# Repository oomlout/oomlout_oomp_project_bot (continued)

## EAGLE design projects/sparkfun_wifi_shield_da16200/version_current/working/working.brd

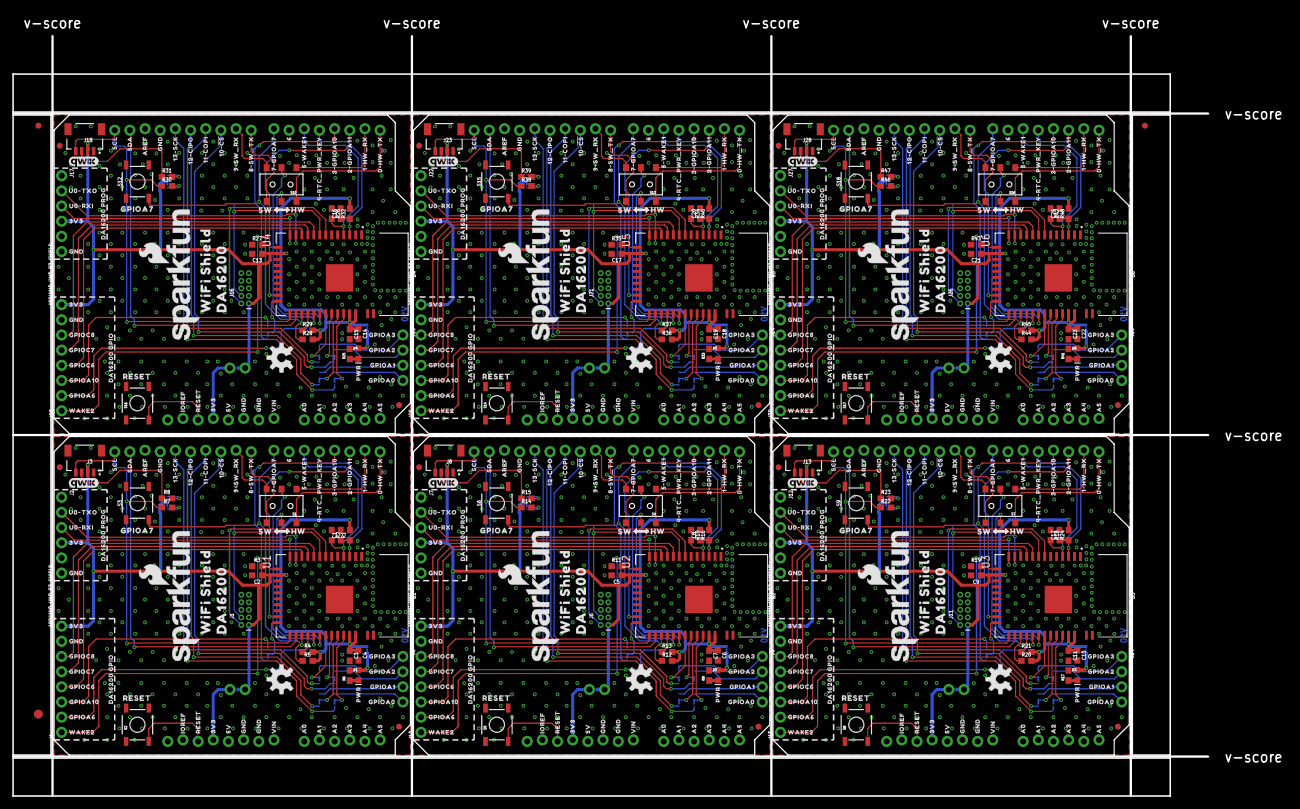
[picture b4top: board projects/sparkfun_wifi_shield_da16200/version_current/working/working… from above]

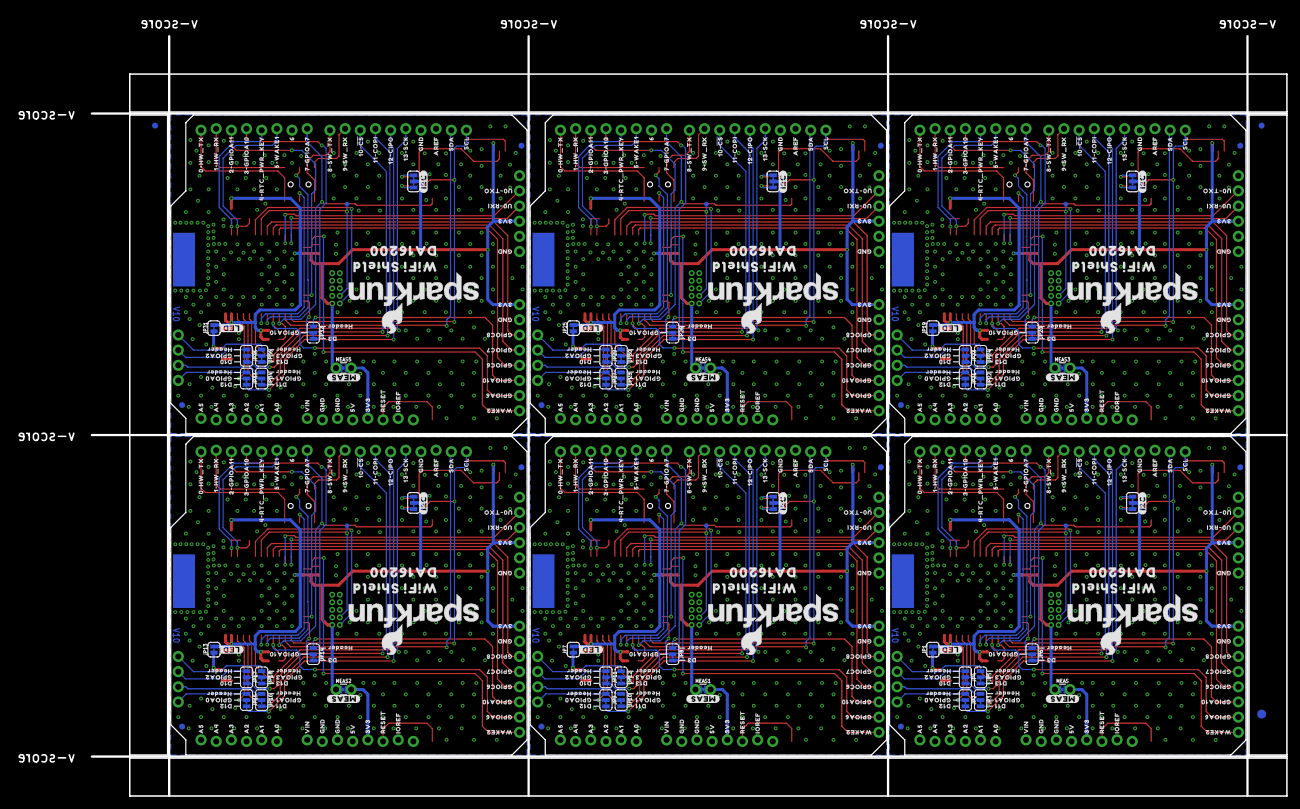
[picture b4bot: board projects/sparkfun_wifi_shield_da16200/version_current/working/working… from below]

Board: 2 copper layers, 200.2 x 127.3 mm, 960 parts (453 on the bottom side), 264 nets.

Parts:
B1, B2, B3, B4, B5, B6: ARDUINO_UNO_R3_SHIELD; UNO_R3_SHIELD_NOLABELS_LOCK
C1, C8, C12, C16, C20, C24: DNP; 0603
C2, C3, C5, C7, C9, C11, C13, C15, C17, C19, C21, C23: 1uF; 0603
C4, C6, C10, C14, C18, C22: 10uF; 0603
D1, D2, D3, D4, D5, D6: RED; LED-0603
E$1, E$2, E$3, E$4: FIDUCIAL-1X2
E$5, E$6: FIDUCIAL-1.5X3
FD1, FD2, FD3, FD4, FD5, FD6, FD7, FD8, FD9, FD10, FD11, FD12, FD13, FD14, FD15, FD16, FD17, FD18, FD19, FD20, FD21, FD22, FD23, FD24: FIDUCIAL1X2; FIDUCIAL-1X2
I2C, I2C1, I2C2, I2C3, I2C4, I2C5: SMT-JUMPER_3_2-NC_TRACE_SILK
J1, J6, J11, J16, J21, J26: CORTEX_JTAG_DEBUG; 2X5-PTH-1.27MM-NO_SILK
J2, J7, J12, J17, J22, J27: 1X06_NO_SILK
J3, J8, J13, J18, J23, J28: QWIIC_RA; JST04_1MM_RA
J4, J10, J15, J20, J25, J30: 1X08_NO_SILK
J5, J9, J14, J19, J24, J29: 1X04_NO_SILK
JP1, JP7, JP13, JP19, JP25, JP31: SMT-JUMPER_2_NC_TRACE_SILK
JP2, JP3, JP4, JP5, JP6, JP8, JP9, JP10, JP11, JP12, JP14, JP15, JP16, JP17, JP18, JP20, JP21, JP22, JP23, JP24, JP26, JP27, JP28, JP29, JP30, JP32, JP33, JP34, JP35, JP36: SMT-JUMPER_3_1-NC_TRACE_SILK
LOGO1, LOGO3, LOGO5, LOGO7, LOGO9, LOGO11, LOGO13, LOGO15, LOGO17, LOGO19, LOGO21, LOGO23: SFE_LOGO_NAME_FLAME.2_INCH; SFE_LOGO_NAME_FLAME_.2
LOGO2, LOGO6, LOGO10, LOGO14, LOGO18, LOGO22: OSHW-LOGOM; OSHW-LOGO-M
LOGO4, LOGO8, LOGO12, LOGO16, LOGO20, LOGO24: QWIIC_LOGO_5MM; QWIIC_5MM
MEAS, MEAS1, MEAS2, MEAS3, MEAS4, MEAS5: COMBO-JUMPER_2_NC_TRACE
R1, R16, R24, R32, R40, R48: DNP; 0603
R2, R3, R4, R5, R7, R8, R10, R11, R12, R13, R14, R15, R18, R19, R20, R21, R22, R23, R26, R27, R28, R29, R30, R31, R34, R35, R36, R37, R38, R39, R42, R43, R44, R45, R46, R47: 4.7k; 0603
R6, R9, R17, R25, R33, R41: 200; 0603
S1, S4, S7, S10, S13, S16: DPDT; SWITCH_DPDT_SMD_AYZ0202
S2, S5, S8, S11, S14, S17: Reset; TACTILE_SWITCH_SMD_5.2MM
S3, S6, S9, S12, S15, S18: TACTILE_SWITCH_SMD_5.2MM
TP1, TP2, TP3, TP4, TP5, TP6: PAD.03X.03
U1, U2, U3, U4, U5, U6: DA16200MOD; XCVR_DA16200MOD-AAC4WA32
U$1, U$16, U$22, U$162, U$239, U$281, U$358, U$400, U$477, U$519, U$596, U$638: IOREF0
U$2, U$19, U$67, U$163, U$240, U$282, U$359, U$401, U$478, U$520, U$597, U$639: RESET0
U$3, U$37, U$39, U$41, U$85, U$87, U$110, U$152, U$155, U$164, U$191, U$193, U$241, U$271, U$274, U$283, U$310, U$312, U$360, U$390, U$393, U$402, U$429, U$431, U$479, U$509, U$512, U$521, U$548, U$550, U$598, U$628, U$631, U$640, U$667, U$669: 3V30
U$4, U$55, U$111, U$165, U$242, U$284, U$361, U$403, U$480, U$522, U$599, U$641: 5V0
U$5, U$6, U$28, U$40, U$52, U$56, U$57, U$79, U$86, U$88, U$112, U$113, U$140, U$153, U$154, U$166, U$167, U$185, U$192, U$194, U$243, U$244, U$259, U$272, U$273, U$285, U$286, U$304, U$311, U$313, U$362, U$363, U$378, U$391, U$392, U$404, U$405, U$423, U$430, U$432, U$481, U$482, U$497, U$510, U$511, U$523, U$524, U$542, U$549, U$551, U$600, U$601, U$616, U$629, U$630, U$642, U$643, U$661, U$668, U$670: GND0
U$7, U$58, U$126, U$168, U$245, U$287, U$364, U$406, U$483, U$525, U$602, U$644: VIN0
U$8, U$59, U$127, U$169, U$246, U$288, U$365, U$407, U$484, U$526, U$603, U$645: A00
U$9, U$60, U$128, U$170, U$247, U$289, U$366, U$408, U$485, U$527, U$604, U$646: A10
U$10, U$61, U$129, U$171, U$248, U$290, U$367, U$409, U$486, U$528, U$605, U$647: A20
U$11, U$62, U$130, U$172, U$249, U$291, U$368, U$410, U$487, U$529, U$606, U$648: A30
U$12, U$63, U$131, U$173, U$250, U$292, U$369, U$411, U$488, U$530, U$607, U$649: A40
U$13, U$64, U$132, U$174, U$251, U$293, U$370, U$412, U$489, U$531, U$608, U$650: A50
U$14, U$65, U$133, U$175, U$252, U$294, U$371, U$413, U$490, U$532, U$609, U$651: 0#HW_TX0
U$15, U$66, U$134, U$176, U$253, U$295, U$372, U$414, U$491, U$533, U$610, U$652: 1#HW_RX0
U$17, U$95, U$158, U$199, U$277, U$318, U$396, U$437, U$515, U$556, U$634, U$675: GPIOA60
U$18, U$70, U$231, U$234, U$350, U$353, U$469, U$472, U$588, U$591, U$707, U$710: 4#RTC_PWR_KEY0
U$20, U$73, U$159, U$179, U$278, U$298, U$397, U$417, U$516, U$536, U$635, U$655: 8#SW_TX0
U$21, U$72, U$135, U$178, U$254, U$297, U$373, U$416, U$492, U$535, U$611, U$654: 7#GPIOA70
U$23, U$33, U$232, U$233, U$351, U$352, U$470, U$471, U$589, U$590, U$708, U$709: 5#WAKE10
U$24, U$75, U$136, U$181, U$255, U$300, U$374, U$419, U$493, U$538, U$612, U$657: 10##CS#0
U$25, U$76, U$137, U$182, U$256, U$301, U$375, U$420, U$494, U$539, U$613, U$658: 11#COPI0
U$26, U$77, U$138, U$183, U$257, U$302, U$376, U$421, U$495, U$540, U$614, U$659: 12#CIPO0
U$27, U$78, U$139, U$184, U$258, U$303, U$377, U$422, U$496, U$541, U$615, U$660: 13#SCK0
U$29, U$80, U$141, U$186, U$260, U$305, U$379, U$424, U$498, U$543, U$617, U$662: AREF0
U$30, U$81, U$142, U$187, U$261, U$306, U$380, U$425, U$499, U$544, U$618, U$663: SDA0
U$31, U$82, U$143, U$188, U$262, U$307, U$381, U$426, U$500, U$545, U$619, U$664: SCL0
U$32, U$74, U$160, U$180, U$279, U$299, U$398, U$418, U$517, U$537, U$636, U$656: 9#SW_RX0
U$34, U$144, U$263, U$382, U$501, U$620: GPIOA70
U$35, U$48, U$235, U$236, U$354, U$355, U$473, U$474, U$592, U$593, U$711, U$712: WAKE20
U$36, U$151, U$270, U$389, U$508, U$627: RESET_0
U$38, U$71, U$161, U$177, U$280, U$296, U$399, U$415, U$518, U$534, U$637, U$653: 60
U$42, U$156, U$275, U$394, U$513, U$632: HW0
U$43, U$157, U$276, U$395, U$514, U$633: SW0
U$44, U$89, U$145, U$195, U$264, U$314, U$383, U$433, U$502, U$552, U$621, U$671: GPIOC80
U$45, U$90, U$146, U$196, U$265, U$315, U$384, U$434, U$503, U$553, U$622, U$672: GPIOC70
U$46, U$91, U$147, U$197, U$266, U$316, U$385, U$435, U$504, U$554, U$623, U$673: GPIOC60
U$47, U$69, U$92, U$148, U$198, U$207, U$267, U$317, U$326, U$386, U$436, U$445, U$505, U$555, U$564, U$624, U$674, U$683: GPIOA100
U$49, U$214, U$333, U$452, U$571, U$690: #I2C#0
U$50, U$109, U$237, U$238, U$356, U$357, U$475, U$476, U$594, U$595, U$713, U$714: 2#GPIOA110
U$51, U$68, U$205, U$206, U$324, U$325, U$443, U$444, U$562, U$563, U$681, U$682: 3#GPIOA100
U$53, U$83, U$149, U$189, U$268, U$308, U$387, U$427, U$506, U$546, U$625, U$665: U0#TXO0
U$54, U$84, U$150, U$190, U$269, U$309, U$388, U$428, U$507, U$547, U$626, U$666: U0#RXI0
U$93, U$115, U$216, U$227, U$335, U$346, U$454, U$465, U$573, U$584, U$692, U$703: GPIOA00
U$94, U$114, U$215, U$228, U$334, U$347, U$453, U$466, U$572, U$585, U$691, U$704: GPIOA10
U$96, U$208, U$327, U$446, U$565, U$684: D30
U$97, U$200, U$319, U$438, U$557, U$676: #LED#0
U$98, U$201, U$320, U$439, U$558, U$677: #MEAS#0
U$99, U$202, U$321, U$440, U$559, U$678: PWR0
U$100, U$107, U$210, U$212, U$329, U$331, U$448, U$450, U$567, U$569, U$686, U$688: WIFI_SHIELD0
U$101, U$108, U$211, U$213, U$330, U$332, U$449, U$451, U$568, U$570, U$687, U$689: DA162000
U$102, U$116, U$217, U$229, U$336, U$348, U$455, U$467, U$574, U$586, U$693, U$705: GPIOA20
U$103, U$117, U$218, U$230, U$337, U$349, U$456, U$468, U$575, U$587, U$694, U$706: GPIOA30
U$104, U$203, U$322, U$441, U$560, U$679: DA16200_GPIO0
U$105, U$204, U$323, U$442, U$561, U$680: DA16200_PROG0
U$106, U$118, U$119, U$120, U$121, U$209, U$219, U$220, U$221, U$222, U$328, U$338, U$339, U$340, U$341, U$447, U$457, U$458, U$459, U$460, U$566, U$576, U$577, U$578, U$579, U$685, U$695, U$696, U$697, U$698: HEADER0
U$122, U$223, U$342, U$461, U$580, U$699: D100
U$123, U$224, U$343, U$462, U$581, U$700: D110
U$124, U$225, U$344, U$463, U$582, U$701: D120
U$125, U$226, U$345, U$464, U$583, U$702: D130

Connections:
3.3V: C2.1, C3.1, C4.1, I2C.2, J1.1, J2.4, J3.2, J4.8, JP1.2, MEAS.1, MEAS.3, R1.2, R4.2, R5.2, U1.15, U1.34, U1.35
3.3V1: C5.1, C6.1, C7.1, I2C1.2, J6.1, J7.4, J8.2, J10.8, JP7.2, MEAS1.1, MEAS1.3, R12.2, R13.2, R16.2, U2.15, U2.34, U2.35
3.3V2: C9.1, C10.1, C11.1, I2C2.2, J11.1, J12.4, J13.2, J15.8, JP13.2, MEAS2.1, MEAS2.3, R20.2, R21.2, R24.2, U3.15, U3.34, U3.35
3.3V3: C13.1, C14.1, C15.1, I2C3.2, J16.1, J17.4, J18.2, J20.8, JP19.2, MEAS3.1, MEAS3.3, R28.2, R29.2, R32.2, U4.15, U4.34, U4.35
3.3V4: C17.1, C18.1, C19.1, I2C4.2, J21.1, J22.4, J23.2, J25.8, JP25.2, MEAS4.1, MEAS4.3, R36.2, R37.2, R40.2, U5.15, U5.34, U5.35
3.3V5: C21.1, C22.1, C23.1, I2C5.2, J26.1, J27.4, J28.2, J30.8, JP31.2, MEAS5.1, MEAS5.3, R44.2, R45.2, R48.2, U6.15, U6.34, U6.35
ARD_GPIOA1: B2.D3, JP8.3
ARD_GPIOA2: B3.D3, JP14.3
ARD_GPIOA3: B4.D3, JP20.3
ARD_GPIOA4: B5.D3, JP26.3
ARD_GPIOA5: B6.D3, JP32.3
ARD_GPIOA10: B1.D3, JP6.3
ARD_HW_RX: B1.RX, S1.1
ARD_HW_RX1: B2.RX, S4.1
ARD_HW_RX2: B3.RX, S7.1
ARD_HW_RX3: B4.RX, S10.1
ARD_HW_RX4: B5.RX, S13.1
ARD_HW_RX5: B6.RX, S16.1
ARD_HW_TX: B1.TX, S1.4
ARD_HW_TX1: B2.TX, S4.4
ARD_HW_TX2: B3.TX, S7.4
ARD_HW_TX3: B4.TX, S10.4
ARD_HW_TX4: B5.TX, S13.4
ARD_HW_TX5: B6.TX, S16.4
ARD_RESET: B1.RES, S2.3
ARD_RESET1: B2.RES, S5.3
ARD_RESET2: B3.RES, S8.3
ARD_RESET3: B4.RES, S11.3
ARD_RESET4: B5.RES, S14.3
ARD_RESET5: B6.RES, S17.3
ARD_SCL: B1.SCL, J3.4, R7.1, U1.24
ARD_SCL1: B2.SCL, J8.4, R14.1, U2.24
ARD_SCL2: B3.SCL, J13.4, R22.1, U3.24
ARD_SCL3: B4.SCL, J18.4, R30.1, U4.24
ARD_SCL4: B5.SCL, J23.4, R38.1, U5.24
ARD_SCL5: B6.SCL, J28.4, R46.1, U6.24
ARD_SDA: B1.SDA, J3.3, R8.1, U1.25
ARD_SDA1: B2.SDA, J8.3, R15.1, U2.25
ARD_SDA2: B3.SDA, J13.3, R23.1, U3.25
ARD_SDA3: B4.SDA, J18.3, R31.1, U4.25
ARD_SDA4: B5.SDA, J23.3, R39.1, U5.25
ARD_SDA5: B6.SDA, J28.3, R47.1, U6.25
ARD_SW_RX: B1.D8, S1.3
ARD_SW_RX1: B2.D8, S4.3
ARD_SW_RX2: B3.D8, S7.3
ARD_SW_RX3: B4.D8, S10.3
ARD_SW_RX4: B5.D8, S13.3
ARD_SW_RX5: B6.D8, S16.3
ARD_SW_TX: B1.D9, S1.6
ARD_SW_TX1: B2.D9, S4.6
ARD_SW_TX2: B3.D9, S7.6
ARD_SW_TX3: B4.D9, S10.6
ARD_SW_TX4: B5.D9, S13.6
ARD_SW_TX5: B6.D9, S16.6
GND: B1.GND@0, B1.GND@1, B1.GND@2, C1.2, C2.2, C3.2, C4.2, J1.3, J1.5, J1.9, J2.6, J3.1, J4.7, R2.1, R3.1, R6.2, S2.1, S3.1, U1.2, U1.ANT_GND, U1.GND
GND1: B2.GND@0, B2.GND@1, B2.GND@2, C5.2, C6.2, C7.2, C8.2, J6.3, J6.5, J6.9, J7.6, J8.1, J10.7, R9.2, R10.1, R11.1, S5.1, S6.1, U2.2, U2.ANT_GND, U2.GND
GND2: B3.GND@0, B3.GND@1, B3.GND@2, C9.2, C10.2, C11.2, C12.2, J11.3, J11.5, J11.9, J12.6, J13.1, J15.7, R17.2, R18.1, R19.1, S8.1, S9.1, U3.2, U3.ANT_GND, U3.GND
GND3: B4.GND@0, B4.GND@1, B4.GND@2, C13.2, C14.2, C15.2, C16.2, J16.3, J16.5, J16.9, J17.6, J18.1, J20.7, R25.2, R26.1, R27.1, S11.1, S12.1, U4.2, U4.ANT_GND, U4.GND
GND4: B5.GND@0, B5.GND@1, B5.GND@2, C17.2, C18.2, C19.2, C20.2, J21.3, J21.5, J21.9, J22.6, J23.1, J25.7, R33.2, R34.1, R35.1, S14.1, S15.1, U5.2, U5.ANT_GND, U5.GND
GND5: B6.GND@0, B6.GND@1, B6.GND@2, C21.2, C22.2, C23.2, C24.2, J26.3, J26.5, J26.9, J27.6, J28.1, J30.7, R41.2, R42.1, R43.1, S17.1, S18.1, U6.2, U6.ANT_GND, U6.GND
GPIOA0: JP2.2, U1.33
GPIOA1: JP3.2, U1.32
GPIOA2: JP4.2, U1.31
GPIOA3: JP5.2, U1.30
GPIOA4: B2.D7, R12.1, S6.3, U2.26
GPIOA5: JP8.2, U2.23
GPIOA6: B2.D2, U2.22
GPIOA7: B1.D7, R5.1, S3.3, U1.26
GPIOA8: JP9.2, U2.33
GPIOA9: JP10.2, U2.32
GPIOA10: JP6.2, U1.23
GPIOA11: B1.D2, U1.22
GPIOA12: JP11.2, U2.31
GPIOA13: JP12.2, U2.30
GPIOA14: B3.D7, R20.1, S9.3, U3.26
GPIOA15: JP14.2, U3.23
GPIOA16: B3.D2, U3.22
GPIOA17: JP15.2, U3.33
GPIOA18: JP16.2, U3.32
GPIOA19: JP17.2, U3.31
GPIOA20: JP18.2, U3.30
GPIOA21: B4.D7, R28.1, S12.3, U4.26
GPIOA22: JP20.2, U4.23
GPIOA23: B4.D2, U4.22
GPIOA24: JP21.2, U4.33
GPIOA25: JP22.2, U4.32
GPIOA26: JP23.2, U4.31
GPIOA27: JP24.2, U4.30
GPIOA28: B5.D7, R36.1, S15.3, U5.26
GPIOA29: JP26.2, U5.23
GPIOA30: B5.D2, U5.22
GPIOA31: JP27.2, U5.33
GPIOA32: JP28.2, U5.32
GPIOA33: JP29.2, U5.31
GPIOA34: JP30.2, U5.30
GPIOA35: B6.D7, R44.1, S18.3, U6.26
GPIOA36: JP32.2, U6.23
GPIOA37: B6.D2, U6.22
GPIOA38: JP33.2, U6.33
GPIOA39: JP34.2, U6.32
GPIOA40: JP35.2, U6.31
GPIOA41: JP36.2, U6.30
HDR_GPIOA0: J5.4, JP2.1
HDR_GPIOA1: J5.3, JP3.1
HDR_GPIOA2: J5.2, JP4.1
HDR_GPIOA3: J5.1, JP5.1
HDR_GPIOA4: J9.4, JP9.1
HDR_GPIOA5: J9.3, JP10.1
HDR_GPIOA6: J4.2, R4.1, U1.27
HDR_GPIOA7: J10.3, JP8.1
HDR_GPIOA8: J10.2, R13.1, U2.27
HDR_GPIOA9: J9.2, JP11.1
HDR_GPIOA10: J4.3, JP6.1
HDR_GPIOA11: J9.1, JP12.1
HDR_GPIOA12: J14.4, JP15.1
HDR_GPIOA13: J14.3, JP16.1
HDR_GPIOA14: J15.3, JP14.1
HDR_GPIOA15: J15.2, R21.1, U3.27
HDR_GPIOA16: J14.2, JP17.1
HDR_GPIOA17: J14.1, JP18.1
HDR_GPIOA18: J19.4, JP21.1
HDR_GPIOA19: J19.3, JP22.1
HDR_GPIOA20: J20.3, JP20.1
HDR_GPIOA21: J20.2, R29.1, U4.27
HDR_GPIOA22: J19.2, JP23.1
HDR_GPIOA23: J19.1, JP24.1
HDR_GPIOA24: J24.4, JP27.1
HDR_GPIOA25: J24.3, JP28.1
HDR_GPIOA26: J25.3, JP26.1
HDR_GPIOA27: J25.2, R37.1, U5.27
HDR_GPIOA28: J24.2, JP29.1
HDR_GPIOA29: J24.1, JP30.1
HDR_GPIOA30: J29.4, JP33.1
HDR_GPIOA31: J29.3, JP34.1
HDR_GPIOA32: J30.3, JP32.1
HDR_GPIOA33: J30.2, R45.1, U6.27
HDR_GPIOA34: J29.2, JP35.1
HDR_GPIOA35: J29.1, JP36.1
HDR_GPIOC1: J10.4, U2.11
HDR_GPIOC2: J10.5, U2.10
HDR_GPIOC3: J10.6, U2.9
HDR_GPIOC4: J15.4, U3.11
HDR_GPIOC5: J15.5, U3.10
HDR_GPIOC6: J4.4, U1.11
HDR_GPIOC7: J4.5, U1.10
HDR_GPIOC8: J4.6, U1.9
HDR_GPIOC9: J15.6, U3.9
HDR_GPIOC10: J20.4, U4.11
HDR_GPIOC11: J20.5, U4.10
HDR_GPIOC12: J20.6, U4.9
HDR_GPIOC13: J25.4, U5.11
HDR_GPIOC14: J25.5, U5.10
HDR_GPIOC15: J25.6, U5.9
HDR_GPIOC16: J30.4, U6.11
HDR_GPIOC17: J30.5, U6.10
HDR_GPIOC18: J30.6, U6.9
HDR_RTC_WAKE1: J10.1, R11.2, U2.14
HDR_RTC_WAKE2: J4.1, R3.2, U1.14
HDR_RTC_WAKE3: J15.1, R19.2, U3.14
HDR_RTC_WAKE4: J20.1, R27.2, U4.14
HDR_RTC_WAKE5: J25.1, R35.2, U5.14
HDR_RTC_WAKE6: J30.1, R43.2, U6.14
unnamed: B1.3.3V, MEAS.2, MEAS.4
unnamed: D1.A, JP1.1
unnamed: I2C.3, R7.2
unnamed: I2C.1, R8.2
unnamed: D1.C, R6.1
unnamed: D2.C, R9.1
unnamed: B2.3.3V, MEAS1.2, MEAS1.4
unnamed: D2.A, JP7.1
unnamed: I2C1.3, R14.2
unnamed: I2C1.1, R15.2
unnamed: D3.C, R17.1
unnamed: B3.3.3V, MEAS2.2, MEAS2.4
unnamed: D3.A, JP13.1
unnamed: I2C2.3, R22.2
unnamed: I2C2.1, R23.2
unnamed: D4.C, R25.1
unnamed: B4.3.3V, MEAS3.2, MEAS3.4
unnamed: D4.A, JP19.1
unnamed: I2C3.3, R30.2
unnamed: I2C3.1, R31.2
unnamed: D5.C, R33.1
unnamed: B5.3.3V, MEAS4.2, MEAS4.4
unnamed: D5.A, JP25.1
unnamed: I2C4.3, R38.2
unnamed: I2C4.1, R39.2
unnamed: D6.C, R41.1
unnamed: B6.3.3V, MEAS5.2, MEAS5.4
unnamed: D6.A, JP31.1
unnamed: I2C5.3, R46.2
unnamed: I2C5.1, R47.2
RTC_PWR_KEY: B1.D4, C1.1, R1.1, U1.3
RTC_PWR_KEY1: B2.D4, C8.1, R16.1, U2.3
RTC_PWR_KEY2: B3.D4, C12.1, R24.1, U3.3
RTC_PWR_KEY3: B4.D4, C16.1, R32.1, U4.3
RTC_PWR_KEY4: B5.D4, C20.1, R40.1, U5.3
RTC_PWR_KEY5: B6.D4, C24.1, R48.1, U6.3
RTC_WAKE1: B1.D5, R2.2, U1.4
RTC_WAKE2: B2.D5, R10.2, U2.4
RTC_WAKE3: B3.D5, R18.2, U3.4
RTC_WAKE4: B4.D5, R26.2, U4.4
RTC_WAKE5: B5.D5, R34.2, U5.4
RTC_WAKE6: B6.D5, R42.2, U6.4
SPI_CIPO: B1.D12, JP2.3
SPI_CIPO1: B2.D12, JP9.3
SPI_CIPO2: B3.D12, JP15.3
SPI_CIPO3: B4.D12, JP21.3
SPI_CIPO4: B5.D12, JP27.3
SPI_CIPO5: B6.D12, JP33.3
SPI_COPI: B1.D11, JP3.3
SPI_COPI1: B2.D11, JP10.3
SPI_COPI2: B3.D11, JP16.3
SPI_COPI3: B4.D11, JP22.3
SPI_COPI4: B5.D11, JP28.3
SPI_COPI5: B6.D11, JP34.3
SPI_CS: B1.D10, JP4.3
SPI_CS1: B2.D10, JP11.3
SPI_CS2: B3.D10, JP17.3
SPI_CS3: B4.D10, JP23.3
SPI_CS4: B5.D10, JP29.3
SPI_CS5: B6.D10, JP35.3
SPI_SCK: B1.D13, JP5.3
SPI_SCK1: B2.D13, JP12.3
SPI_SCK2: B3.D13, JP18.3
SPI_SCK3: B4.D13, JP24.3
SPI_SCK4: B5.D13, JP30.3
SPI_SCK5: B6.D13, JP36.3
TCLK: J1.4, TP1.1, U1.8
TCLK1: J6.4, TP2.1, U2.8
TCLK2: J11.4, TP3.1, U3.8
TCLK3: J16.4, TP4.1, U4.8
TCLK4: J21.4, TP5.1, U5.8
TCLK5: J26.4, TP6.1, U6.8
TMS: J1.2, U1.7
TMS1: J6.2, U2.7
TMS2: J11.2, U3.7
TMS3: J16.2, U4.7
TMS4: J21.2, U5.7
TMS5: J26.2, U6.7
U0RXI: J2.3, U1.13
U0RXI1: J7.3, U2.13
U0RXI2: J12.3, U3.13
U0RXI3: J17.3, U4.13
U0RXI4: J22.3, U5.13
U0RXI5: J27.3, U6.13
U0TXO: J2.2, U1.12
U0TXO1: J7.2, U2.12
U0TXO2: J12.2, U3.12
U0TXO3: J17.2, U4.12
U0TXO4: J22.2, U5.12
U0TXO5: J27.2, U6.12
U1RXI: S1.5, U1.28
U1RXI1: S4.5, U2.28
U1RXI2: S7.5, U3.28
U1RXI3: S10.5, U4.28
U1RXI4: S13.5, U5.28
U1RXI5: S16.5, U6.28
U1TXO: S1.2, U1.29
U1TXO1: S4.2, U2.29
U1TXO2: S7.2, U3.29
U1TXO3: S10.2, U4.29
U1TXO4: S13.2, U5.29
U1TXO5: S16.2, U6.29

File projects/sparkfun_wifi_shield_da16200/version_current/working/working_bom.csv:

"Id";"Designator";"Footprint";"Quantity";"Designation";"Supplier and ref";
1;"U$630,U$378,U$600,U$243,U$391,U$629,U$40,U$392,U$140,U$113,U$616,U$511,U$273,U$497,U$244,U$28,U$259,U$482,U$362,U$272,U$112,U$5,U$6,U$510,U$481,U$52,U$153,U$154,U$601,U$363,U$194,U$79,U$185,U$56,U$643,U$88,U$57,U$542,U$661,U$404,U$313,U$551,U$192,U$423,U$668,U$549,U$166,U$285,U$167,U$86,U$432,U$524,U$304,U$311,U$642,U$405,U$670,U$430,U$523,U$286";"GND0";60;"";;;
2;"S6,S15,S9,S3,S12,S18";"TACTILE_SWITCH_SMD_5.2MM";6;"";;;
3;"C13,C3,C21,C11,C17,C23,C7,C2,C5,C9,C15,C19";"0603";12;"1uF";;;
4;"J29,J5,J19,J14,J9,J24";"1X04_NO_SILK";6;"";;;
5;"C8,R48,R32,R24,C16,C20,C12,R16,R1,C1,R40,C24";"0603";12;"DNP";;;
6;"U$585,U$228,U$466,U$94,U$704,U$347,U$334,U$114,U$691,U$215,U$572,U$453";"GPIOA10";12;"";;;
7;"LOGO21,LOGO1,LOGO13,LOGO5,LOGO9,LOGO17,LOGO7,LOGO23,LOGO3,LOGO15,LOGO11,LOGO19";"SFE_LOGO_NAME_FLAME_.2";12;"SFE_LOGO_NAME_FLAME.2_INCH";;;
8;"E$3,E$1,E$4,E$2";"FIDUCIAL-1X2";4;"";;;
9;"U$589,U$232,U$23,U$470,U$351,U$708,U$352,U$233,U$471,U$709,U$33,U$590";"5#WAKE10";12;"";;;
10;"U$350,U$231,U$707,U$469,U$18,U$588,U$591,U$353,U$70,U$234,U$472,U$710";"4#RTC_PWR_KEY0";12;"";;;
11;"U$625,U$53,U$387,U$149,U$268,U$506,U$665,U$189,U$83,U$308,U$427,U$546";"U0#TXO0";12;"";;;
12;"U$133,U$14,U$490,U$252,U$371,U$609,U$175,U$294,U$532,U$651,U$413,U$65";"0#HW_TX0";12;"";;;
13;"U$10,U$605,U$486,U$129,U$248,U$367,U$409,U$290,U$528,U$647,U$61,U$171";"A20";12;"";;;
14;"U$142,U$380,U$499,U$30,U$618,U$261,U$663,U$187,U$425,U$306,U$544,U$81";"SDA0";12;"";;;
15;"LOGO4,LOGO16,LOGO12,LOGO24,LOGO8,LOGO20";"QWIIC_5MM";6;"QWIIC_LOGO_5MM";;;
16;"U$368,U$130,U$487,U$249,U$11,U$606,U$62,U$410,U$172,U$648,U$529,U$291";"A30";12;"";;;
17;"U$394,U$513,U$632,U$156,U$42,U$275";"HW0";6;"";;;
18;"J12,J17,J2,J22,J27,J7";"1X06_NO_SILK";6;"";;;
19;"C4,C22,C18,C10,C14,C6";"0603";6;"10uF";;;
20;"U$388,U$626,U$54,U$269,U$507,U$150,U$309,U$666,U$84,U$547,U$428,U$190";"U0#RXI0";12;"";;;
21;"U$203,U$322,U$441,U$679,U$104,U$560";"DA16200_GPIO0";6;"";;;
22;"U$610,U$491,U$253,U$372,U$15,U$134,U$414,U$533,U$295,U$652,U$66,U$176";"1#HW_RX0";12;"";;;
23;"U$680,U$105,U$204,U$561,U$442,U$323";"DA16200_PROG0";6;"";;;
24;"U$598,U$241,U$628,U$631,U$274,U$479,U$41,U$271,U$155,U$110,U$37,U$393,U$360,U$390,U$152,U$3,U$512,U$509,U$669,U$431,U$429,U$640,U$667,U$85,U$310,U$193,U$548,U$87,U$283,U$191,U$521,U$550,U$164,U$39,U$402,U$312";"3V30";36;"";;;
25;"J28,J13,J18,J23,J8,J3";"JST04_1MM_RA";6;"QWIIC_RA";;;
26;"R5,R7,R18,R15,R30,R31,R10,R8,R26,R37,R4,R19,R46,R2,R22,R29,R45,R39,R3,R11,R43,R21,R28,R44,R42,R20,R36,R47,R14,R13,R34,R27,R23,R35,R12,R38";"0603";36;"4.7k";;;
27;"J15,J4,J30,J25,J10,J20";"1X08_NO_SILK";6;"";;;
28;"U$383,U$502,U$44,U$621,U$264,U$145,U$552,U$671,U$195,U$89,U$314,U$433";"GPIOC80";12;"";;;
29;"B2,B1,B3,B4,B6,B5";"UNO_R3_SHIELD_NOLABELS_LOCK";6;"ARDUINO_UNO_R3_SHIELD";;;
30;"U$636,U$279,U$517,U$32,U$398,U$160,U$299,U$180,U$74,U$656,U$418,U$537";"9#SW_RX0";12;"";;;
31;"U$25,U$613,U$375,U$494,U$256,U$137,U$301,U$658,U$539,U$76,U$420,U$182";"11#COPI0";12;"";;;
32;"U$38,U$161,U$518,U$280,U$399,U$637,U$415,U$296,U$653,U$177,U$534,U$71";"60";12;"";;;
33;"U$348,U$229,U$102,U$705,U$586,U$467,U$693,U$217,U$574,U$336,U$116,U$455";"GPIOA20";12;"";;;
34;"FD11,FD7,FD15,FD3,FD23,FD9,FD19,FD5,FD17,FD21,FD13,FD1,FD12,FD4,FD6,FD18,FD16,FD14,FD8,FD10,FD22,FD2,FD20,FD24";"FIDUCIAL-1X2";24;"FIDUCIAL1X2";;;
35;"U6,U4,U5,U1,U3,U2";"XCVR_DA16200MOD-AAC4WA32";6;"DA16200MOD";;;
36;"D2,D3,D6,D1,D4,D5";"LED-0603";6;"RED";;;
37;"U$46,U$385,U$147,U$266,U$504,U$623,U$554,U$673,U$91,U$197,U$435,U$316";"GPIOC60";12;"";;;
38;"U$687,U$108,U$568,U$449,U$211,U$330,U$213,U$570,U$689,U$451,U$101,U$332";"DA162000";12;"";;;
39;"U$382,U$34,U$263,U$501,U$144,U$620";"GPIOA70";6;"";;;
40;"U$128,U$366,U$485,U$604,U$9,U$247,U$408,U$170,U$527,U$60,U$289,U$646";"A10";12;"";;;
41;"U$614,U$376,U$138,U$495,U$26,U$257,U$540,U$183,U$302,U$421,U$659,U$77";"12#CIPO0";12;"";;;
42;"U$602,U$126,U$364,U$483,U$245,U$7,U$287,U$406,U$644,U$58,U$168,U$525";"VIN0";12;"";;;
43;"U$597,U$2,U$478,U$359,U$67,U$240,U$282,U$401,U$520,U$163,U$639,U$19";"RESET0";12;"";;;
44;"U$617,U$260,U$29,U$498,U$141,U$379,U$662,U$424,U$80,U$543,U$186,U$305";"AREF0";12;"";;;
45;"R6,R41,R9,R25,R33,R17";"0603";6;"200";;;
46;"U$596,U$239,U$358,U$477,U$1,U$22,U$519,U$281,U$400,U$638,U$162,U$16";"IOREF0";12;"";;;
47;"LOGO14,LOGO6,LOGO22,LOGO10,LOGO2,LOGO18";"OSHW-LOGO-M";6;"OSHW-LOGOM";;;
48;"U$251,U$608,U$13,U$489,U$132,U$370,U$412,U$531,U$650,U$174,U$64,U$293";"A50";12;"";;;
49;"U$496,U$615,U$139,U$377,U$258,U$27,U$660,U$184,U$541,U$78,U$422,U$303";"13#SCK0";12;"";;;
50;"U$389,U$36,U$270,U$151,U$627,U$508";"RESET_0";6;"";;;
51;"U$635,U$278,U$20,U$516,U$159,U$397,U$73,U$536,U$417,U$298,U$655,U$179";"8#SW_TX0";12;"";;;
52;"U$714,U$109,U$238,U$476,U$595,U$357,U$237,U$50,U$594,U$475,U$713,U$356";"2#GPIOA110";12;"";;;
53;"J11,J6,J16,J26,J21,J1";"2X5-PTH-1.27MM-NO_SILK";6;"CORTEX_JTAG_DEBUG";;;
54;"U$45,U$622,U$265,U$384,U$146,U$503,U$434,U$553,U$196,U$672,U$315,U$90";"GPIOC70";12;"";;;
55;"U$277,U$17,U$396,U$634,U$158,U$515,U$318,U$95,U$675,U$437,U$556,U$199";"GPIOA60";12;"";;;
56;"U$276,U$395,U$157,U$514,U$633,U$43";"SW0";6;"";;;
57;"E$5,E$6";"FIDUCIAL-1.5X3";2;"";;;
58;"U$127,U$365,U$603,U$484,U$8,U$246,U$645,U$169,U$407,U$288,U$59,U$526";"A00";12;"";;;
59;"U$324,U$205,U$681,U$51,U$443,U$562,U$68,U$682,U$325,U$444,U$563,U$206";"3#GPIOA100";12;"";;;
60;"U$492,U$254,U$135,U$611,U$21,U$373,U$72,U$654,U$178,U$297,U$535,U$416";"7#GPIOA70";12;"";;;
61;"U$493,U$374,U$136,U$24,U$612,U$255,U$538,U$657,U$300,U$419,U$181,U$75";"10##CS#0";12;"";;;
62;"U$210,U$329,U$107,U$448,U$567,U$686,U$688,U$100,U$450,U$212,U$569,U$331";"WIFI_SHIELD0";12;"";;;
63;"U$619,U$143,U$31,U$500,U$381,U$262,U$545,U$188,U$664,U$307,U$426,U$82";"SCL0";12;"";;;
64;"U$465,U$703,U$227,U$584,U$93,U$346,U$573,U$115,U$335,U$454,U$692,U$216";"GPIOA00";12;"";;;
65;"U$111,U$4,U$480,U$242,U$599,U$361,U$641,U$165,U$284,U$403,U$55,U$522";"5V0";12;"";;;
66;"U$468,U$349,U$587,U$230,U$706,U$103,U$456,U$694,U$218,U$117,U$337,U$575";"GPIOA30";12;"";;;
67;"U$505,U$386,U$624,U$267,U$47,U$148,U$683,U$564,U$326,U$92,U$69,U$317,U$445,U$555,U$674,U$436,U$207,U$198";"GPIOA100";18;"";;;
68;"U$559,U$99,U$321,U$440,U$678,U$202";"PWR0";6;"";;;
69;"S5,S11,S2,S17,S14,S8";"TACTILE_SWITCH_SMD_5.2MM";6;"Reset";;;
70;"S4,S13,S16,S7,S10,S1";"SWITCH_DPDT_SMD_AYZ0202";6;"DPDT";;;
71;"U$473,U$35,U$592,U$354,U$711,U$235,U$712,U$236,U$48,U$593,U$355,U$474";"WAKE20";12;"";;;
72;"U$12,U$488,U$607,U$369,U$250,U$131,U$530,U$173,U$63,U$292,U$649,U$411";"A40";12;"";;;
73;"JP14,JP16,JP2,JP8,JP29,JP35,JP34,JP33,JP23,JP32,JP4,JP9,JP36,JP21,JP3,JP6,JP27,JP10,JP30,JP11,JP28,JP17,JP20,JP5,JP22,JP12,JP15,JP26,JP18,JP24";"SMT-JUMPER_3_1-NC_TRACE_SILK";30;"";;;
74;"U$106,U$328,U$685,U$338,U$341,U$220,U$221,U$222,U$697,U$579,U$566,U$695,U$457,U$578,U$219,U$209,U$458,U$340,U$119,U$576,U$339,U$120,U$121,U$459,U$118,U$577,U$698,U$460,U$447,U$696";"HEADER0";30;"";;;
75;"JP13,JP19,JP31,JP25,JP7,JP1";"SMT-JUMPER_2_NC_TRACE_SILK";6;"";;;
76;"U$581,U$343,U$123,U$700,U$462,U$224";"D110";6;"";;;
77;"U$125,U$702,U$226,U$583,U$345,U$464";"D130";6;"";;;
78;"U$558,U$677,U$320,U$98,U$201,U$439";"#MEAS#0";6;"";;;
79;"U$557,U$438,U$97,U$200,U$676,U$319";"#LED#0";6;"";;;
80;"I2C3,I2C2,I2C0,I2C4,I2C1,I2C5";"SMT-JUMPER_3_2-NC_TRACE_SILK";6;"";;;
81;"U$461,U$223,U$342,U$122,U$699,U$580";"D100";6;"";;;
82;"U$452,U$571,U$49,U$690,U$214,U$333";"#I2C#0";6;"";;;
83;"TP3,TP2,TP6,TP1,TP4,TP5";"PAD.03X.03";6;"";;;
84;"MEAS1,MEAS3,MEAS2,MEAS0,MEAS4,MEAS5";"COMBO-JUMPER_2_NC_TRACE";6;"";;;
85;"U$701,U$124,U$225,U$463,U$582,U$344";"D120";6;"";;;
86;"U$96,U$565,U$208,U$446,U$327,U$684";"D30";6;"";;;

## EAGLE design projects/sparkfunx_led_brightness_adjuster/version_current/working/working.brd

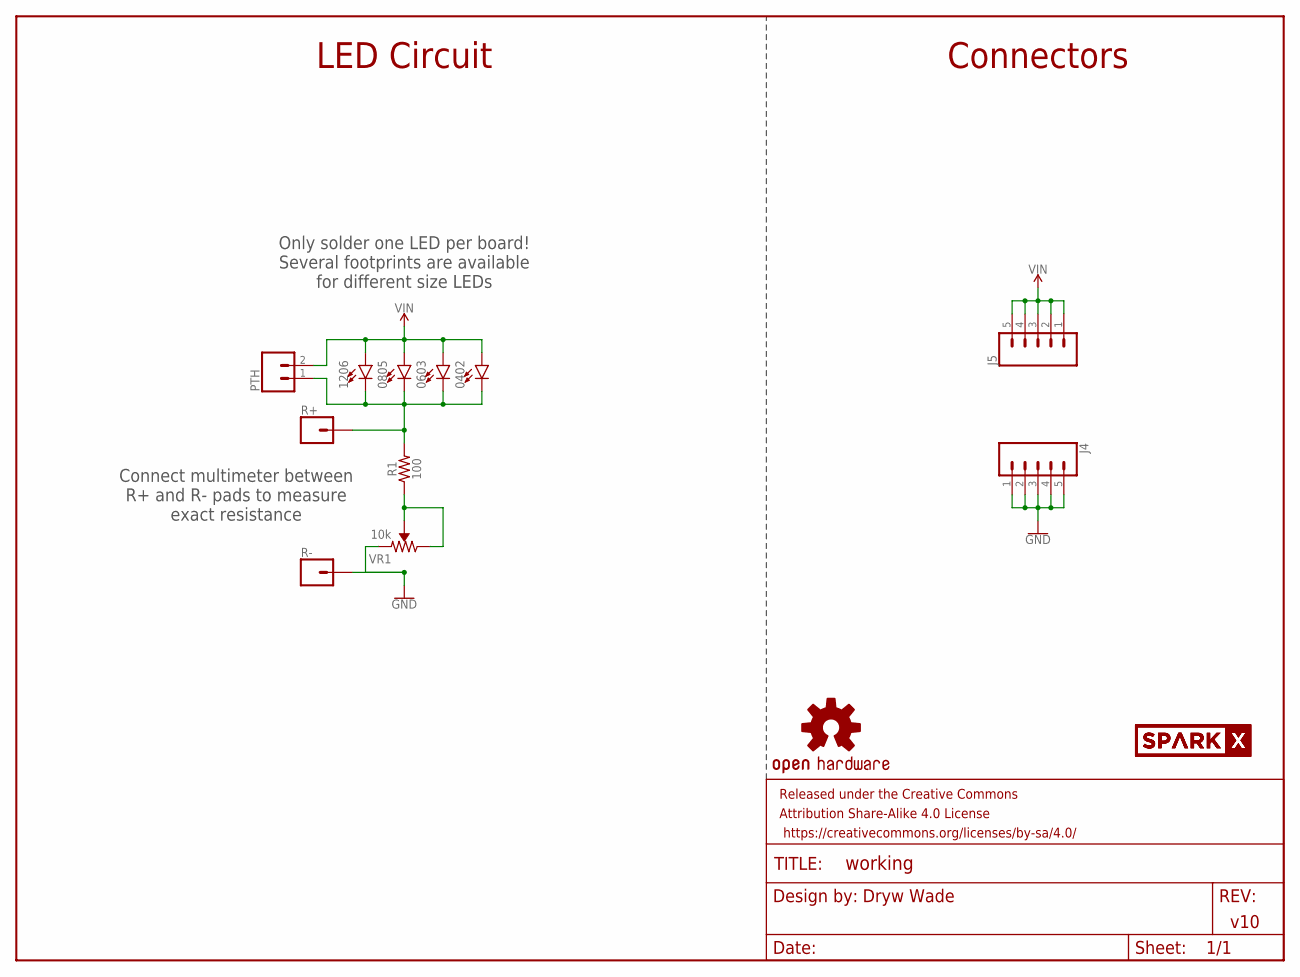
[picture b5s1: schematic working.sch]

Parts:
0402: RED; LED-0402
0603: RED; LED-0603
0805: RED; LED-0805
1206: RED; LED-1206
FRAME1: FRAME-LETTER; CREATIVE_COMMONS
J4, J5: CONN_05; 1X05
LOGO2: OSHW-LOGOS; OSHW-LOGO-S
PTH: CONN_02; 1X02
R1: 100; AXIAL-0.3
R+: CONN_01; 1X01
R-: CONN_01; 1X01
U$26, U$27: SPARKX-LOGO5; SPARKX-LARGE
VR1: 10k; TRIMPOT-PTH-3386U

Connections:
GND: J4.1, J4.2, J4.3, J4.4, J4.5, R-.1, VR1.1 (CCW)
unnamed: 0402.C, 0603.C, 0805.C, 1206.C, PTH.1, R1.P$2 (2), R+.1
unnamed: R1.P$1 (1), VR1.2 (WIPER), VR1.3 (CW)
VIN: 0402.A, 0603.A, 0805.A, 1206.A, J5.1, J5.2, J5.3, J5.4, J5.5, PTH.2

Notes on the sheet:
Dryw Wade
v10
Connectors
LED Circuit
Connect multimeter between R+ and R- pads to measure exact resistance
Only solder one LED per board\! Several footprints are available for different size LEDs

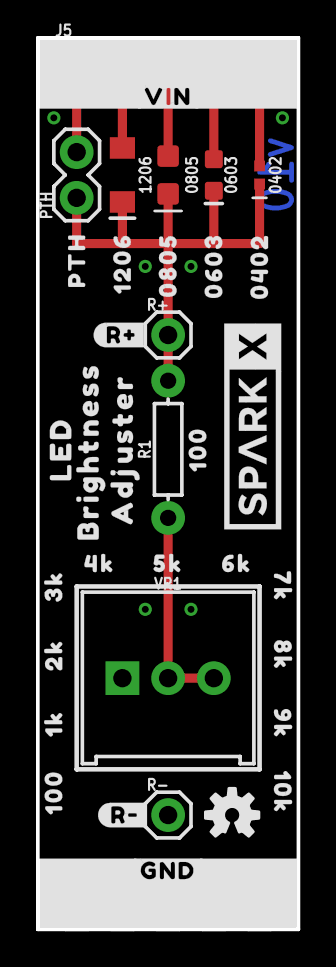
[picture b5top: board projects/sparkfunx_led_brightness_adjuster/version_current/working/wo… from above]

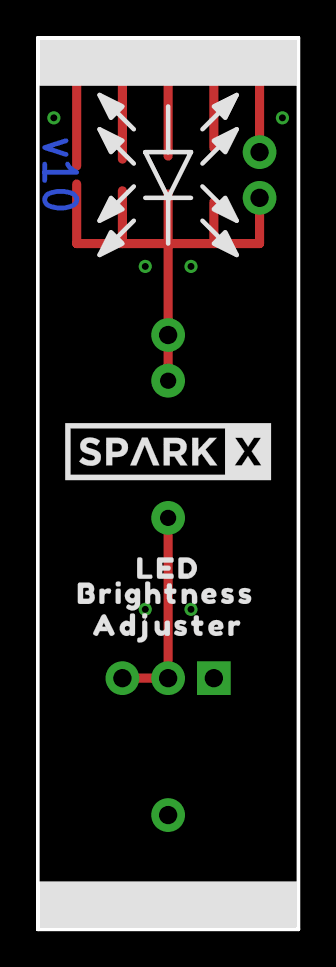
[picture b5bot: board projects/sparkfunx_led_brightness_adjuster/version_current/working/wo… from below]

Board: 2 copper layers, 14.5 x 49.5 mm, 42 parts (4 on the bottom side), 4 nets.

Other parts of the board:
U$1: 4K0
U$2: 6K0
U$3: 1K0
U$4, U$8: 1000
U$5: 10K0
U$6: #VIN#0
U$7: 5K0
U$9: #R##0
U$10, U$23: ADJUSTER0
U$11: #GND#0
U$12: 3K0
U$13: 2K0
U$14: 7K0
U$15: 8K0
U$16: 9K0
U$17: PTH0
U$18: 12060
U$19: 08050
U$20: 04020
U$21: 06030
U$22, U$24: LED0
U$25, U$28: BRIGHTNESS0
U$29: #R##2

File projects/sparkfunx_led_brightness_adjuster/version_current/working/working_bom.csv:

"Id";"Designator";"Footprint";"Quantity";"Designation";"Supplier and ref";
1;"VR1";"TRIMPOT-PTH-3386U";1;"10k";;;
2;"R1";"AXIAL-0.3";1;"100";;;
3;"J5,J4";"1X05";2;"";;;
4;"U$18";"12060";1;"";;;
5;"U$5";"10K0";1;"";;;
6;"PTH0";"1X02";1;"";;;
7;"U$16";"9K0";1;"";;;
8;"U$12";"3K0";1;"";;;
9;"U$17";"PTH0";1;"";;;
10;"U$7";"5K0";1;"";;;
11;"U$26,U$27";"SPARKX-LARGE";2;"SPARKX-LOGO5";;;
12;"U$3";"1K0";1;"";;;
13;"U$14";"7K0";1;"";;;
14;"U$11";"#GND#0";1;"";;;
15;"U$1";"4K0";1;"";;;
16;"U$23,U$10";"ADJUSTER0";2;"";;;
17;"U$21";"06030";1;"";;;
18;"U$13";"2K0";1;"";;;
19;"UNK0402";"LED-0402";1;"RED";;;
20;"U$19";"08050";1;"";;;
21;"U$22,U$24";"LED0";2;"";;;
22;"UNK0603";"LED-0603";1;"RED";;;
23;"R-0,R+0";"1X01";2;"";;;
24;"U$6";"#VIN#0";1;"";;;
25;"U$20";"04020";1;"";;;
26;"LOGO2";"OSHW-LOGO-S";1;"OSHW-LOGOS";;;
27;"U$4,U$8";"1000";2;"";;;
28;"U$9";"#R##0";1;"";;;
29;"UNK0805";"LED-0805";1;"RED";;;
30;"FRAME1";"CREATIVE_COMMONS";1;"FRAME-LETTER";;;
31;"U$2";"6K0";1;"";;;
32;"U$28,U$25";"BRIGHTNESS0";2;"";;;
33;"U$29";"#R##2";1;"";;;
34;"U$15";"8K0";1;"";;;
35;"UNK1206";"LED-1206";1;"RED";;;
